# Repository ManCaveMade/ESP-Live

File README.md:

# ESP-Live
An ESP8266 (ESP-12F) board with USB and Mains power supply for home automation applications.

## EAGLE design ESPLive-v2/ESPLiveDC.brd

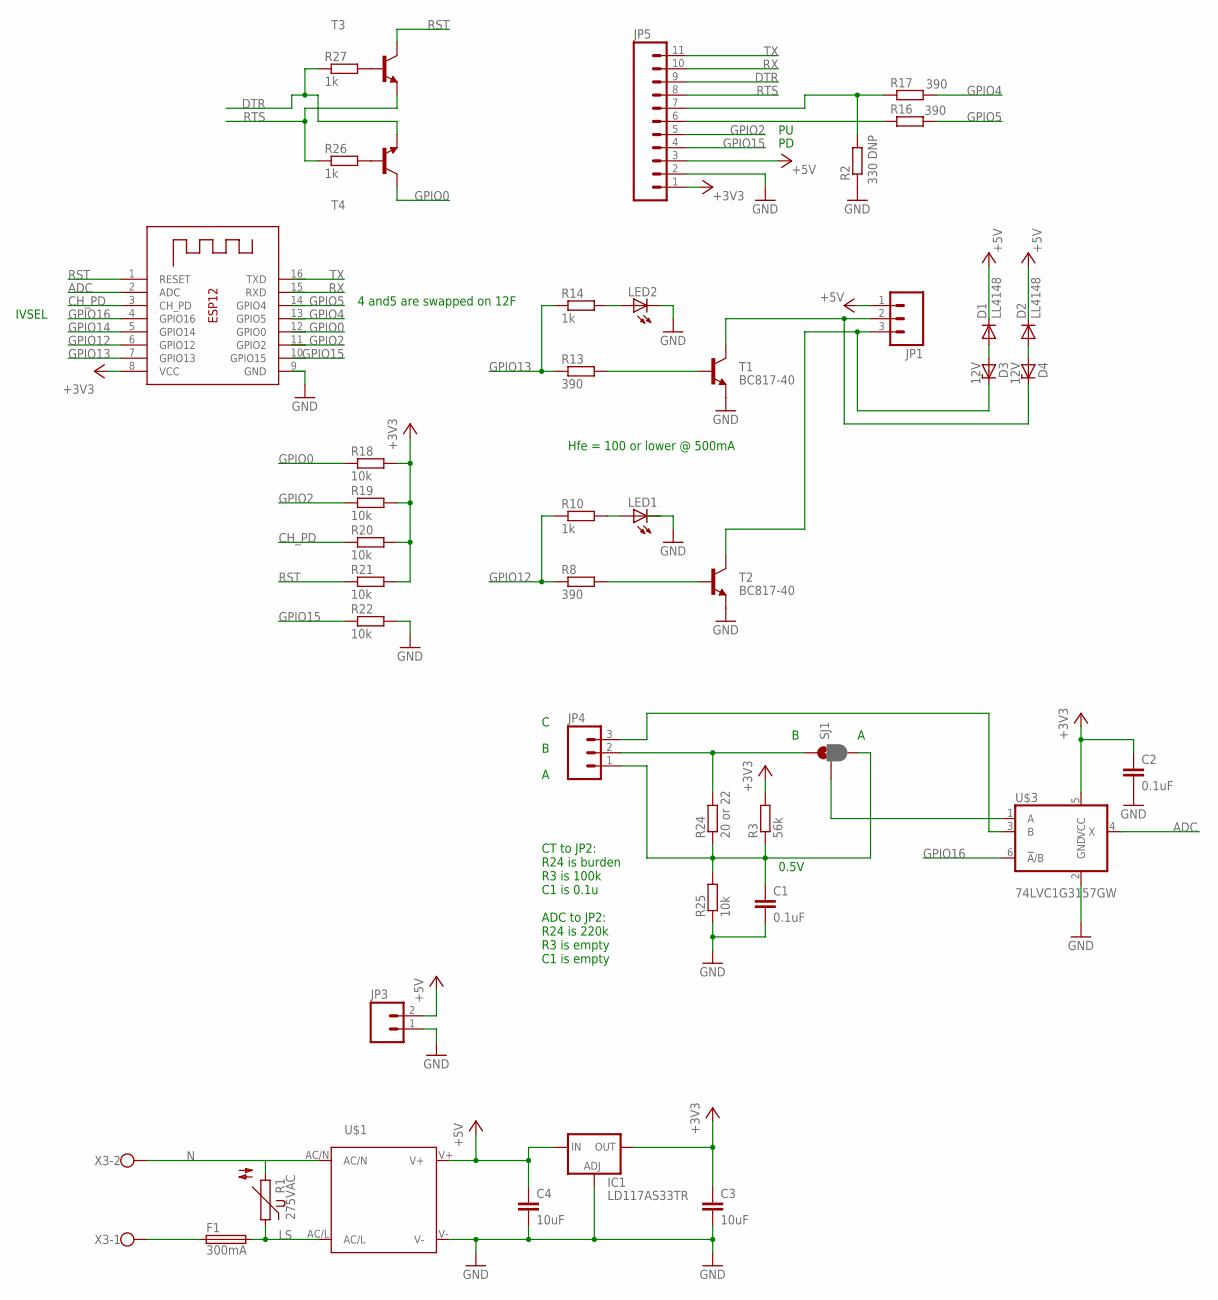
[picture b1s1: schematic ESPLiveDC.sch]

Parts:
C1, C2: 0.1uF; C0603
C3, C4: 10uF; C0805
D1, D2: LL4148; SOD80C
D3, D4: 12V; SOD80C
F1: 300mA; TE5
IC1: LD117AS33TR; SOT223
JP1, JP4: M03POLAR_LOCK; MOLEX-1X3_LOCK
JP3: M02POLAR_LOCK; MOLEX-1X2_LOCK
JP5: M11LOCK; 1X11_LOCK
LED1, LED2: LED1206; LED-1206
R1: 275VAC; P593
R2: 330 DNP; R0603
R3: 56k; R0603
R8, R13, R16, R17: 390; R0603
R10, R14, R26, R27: 1k; R0603
R18, R19, R20, R21, R22, R25: 10k; R0603
R24: 20 or 22; R1206
SJ1: JUMPER-PAD-3-2OF3_NC_BY_PASTE; PAD-JUMPER-3-2OF3_NC_BY_PASTE_YES_SILK_FULL_BOX
T1, T2: BC817-40; SOT23-BEC
T3, T4: BC817-40-NPN-SOT23-BEC; SOT23-BEC
U$1: IRM_01/02_SMDIRM_01/02_SMD; IRM_01/02_SMD
U$3: 74LVC1G3157GW; SOT363
X1: ESP-12
X3: W237-102

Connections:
+3V3: C2.1, C3.1, IC1.4 (OUT), JP5.1, R3.2, R18.2, R19.2, R20.2, R21.2, U$3.5 (VCC), X1.8 (VCC)
+5V: C4.1, D1.C, D2.C, IC1.3 (IN), JP1.1, JP3.2, JP5.3, U$1.V+
ADC: U$3.4 (X), X1.2 (ADC)
CH_PD: R20.1, X1.3 (CH_PD)
DTR: JP5.9, R27.1, T4.E
GND: C1.2, C2.2, C3.2, C4.2, IC1.1 (ADJ), JP3.1, JP5.2, LED1.C, LED2.C, R2.1, R22.2, R25.1, T1.E, T2.E, U$1.V-, U$3.2 (GND), X1.9 (GND)
GPIO0: R18.1, T4.C, X1.12 (GPIO0)
GPIO2: JP5.5, R19.1, X1.11 (GPIO2)
GPIO4: R17.2, X1.13 (GPIO5)
GPIO5: R16.2, X1.14 (GPIO4)
GPIO12: R8.1, R10.1, X1.6 (GPIO12)
GPIO13: R13.1, R14.1, X1.7 (GPIO13)
GPIO14: X1.5 (GPIO14)
GPIO15: JP5.4, R22.1, X1.10 (GPIO15)
GPIO16: U$3.6 (!A!/B), X1.4 (GPIO16)
LS: F1.2, R1.1, U$1.AC/L
N: R1.2, U$1.AC/N, X3.2
unnamed: R13.2, T1.B
unnamed: LED1.A, R10.2
unnamed: R8.2, T2.B
unnamed: D4.C, JP1.2, T1.C
unnamed: D3.C, JP1.3, T2.C
unnamed: F1.1, X3.1
unnamed: D1.A, D3.A
unnamed: D2.A, D4.A
unnamed: C1.1, JP4.1, R3.1, R24.1, R25.2, SJ1.3
unnamed: JP4.2, R24.2, SJ1.1
unnamed: SJ1.2, U$3.1 (A)
unnamed: JP4.3, U$3.3 (B)
unnamed: LED2.A, R14.2
unnamed: JP5.6, R16.1
unnamed: JP5.7, R2.2, R17.1
unnamed: R26.2, T4.B
unnamed: R27.2, T3.B
RST: R21.1, T3.C, X1.1 (RESET)
RTS: JP5.8, R26.1, T3.E
RX: JP5.10, X1.15 (RXD)
TX: JP5.11, X1.16 (TXD)

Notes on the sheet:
IVSEL
Hfe = 100 or lower @ 500mA
4 and5 are swapped on 12F
CT to JP2: R24 is burden R3 is 100k C1 is 0.1u ADC to JP2: R24 is 220k R3 is empty C1 is empty
0.5V

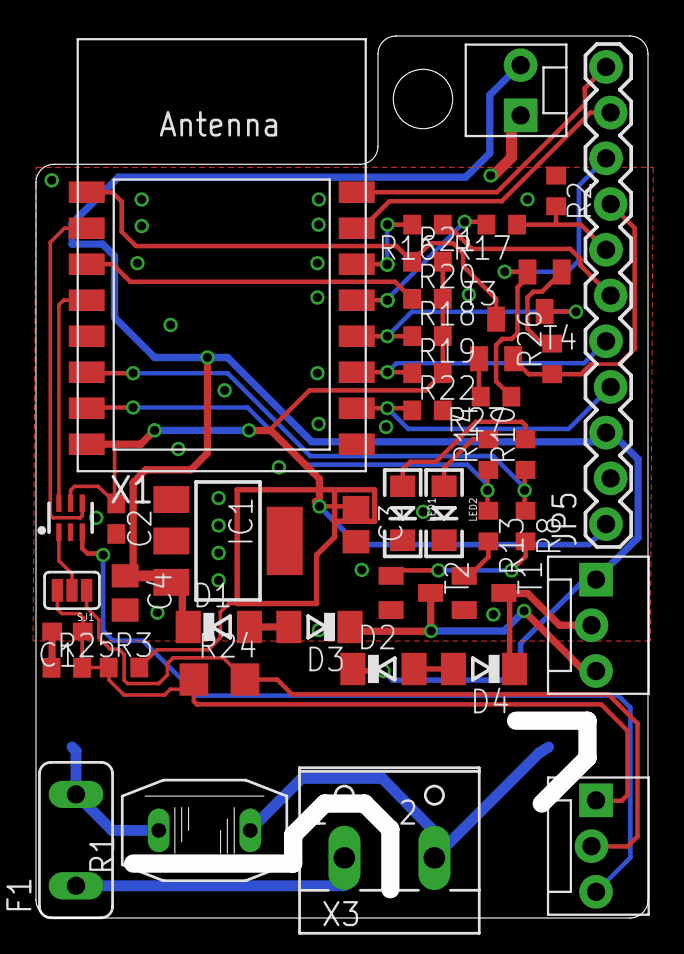
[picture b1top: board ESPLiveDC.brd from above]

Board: 2 copper layers, 34.0 x 49.0 mm, 43 parts (1 on the bottom side), 37 nets.

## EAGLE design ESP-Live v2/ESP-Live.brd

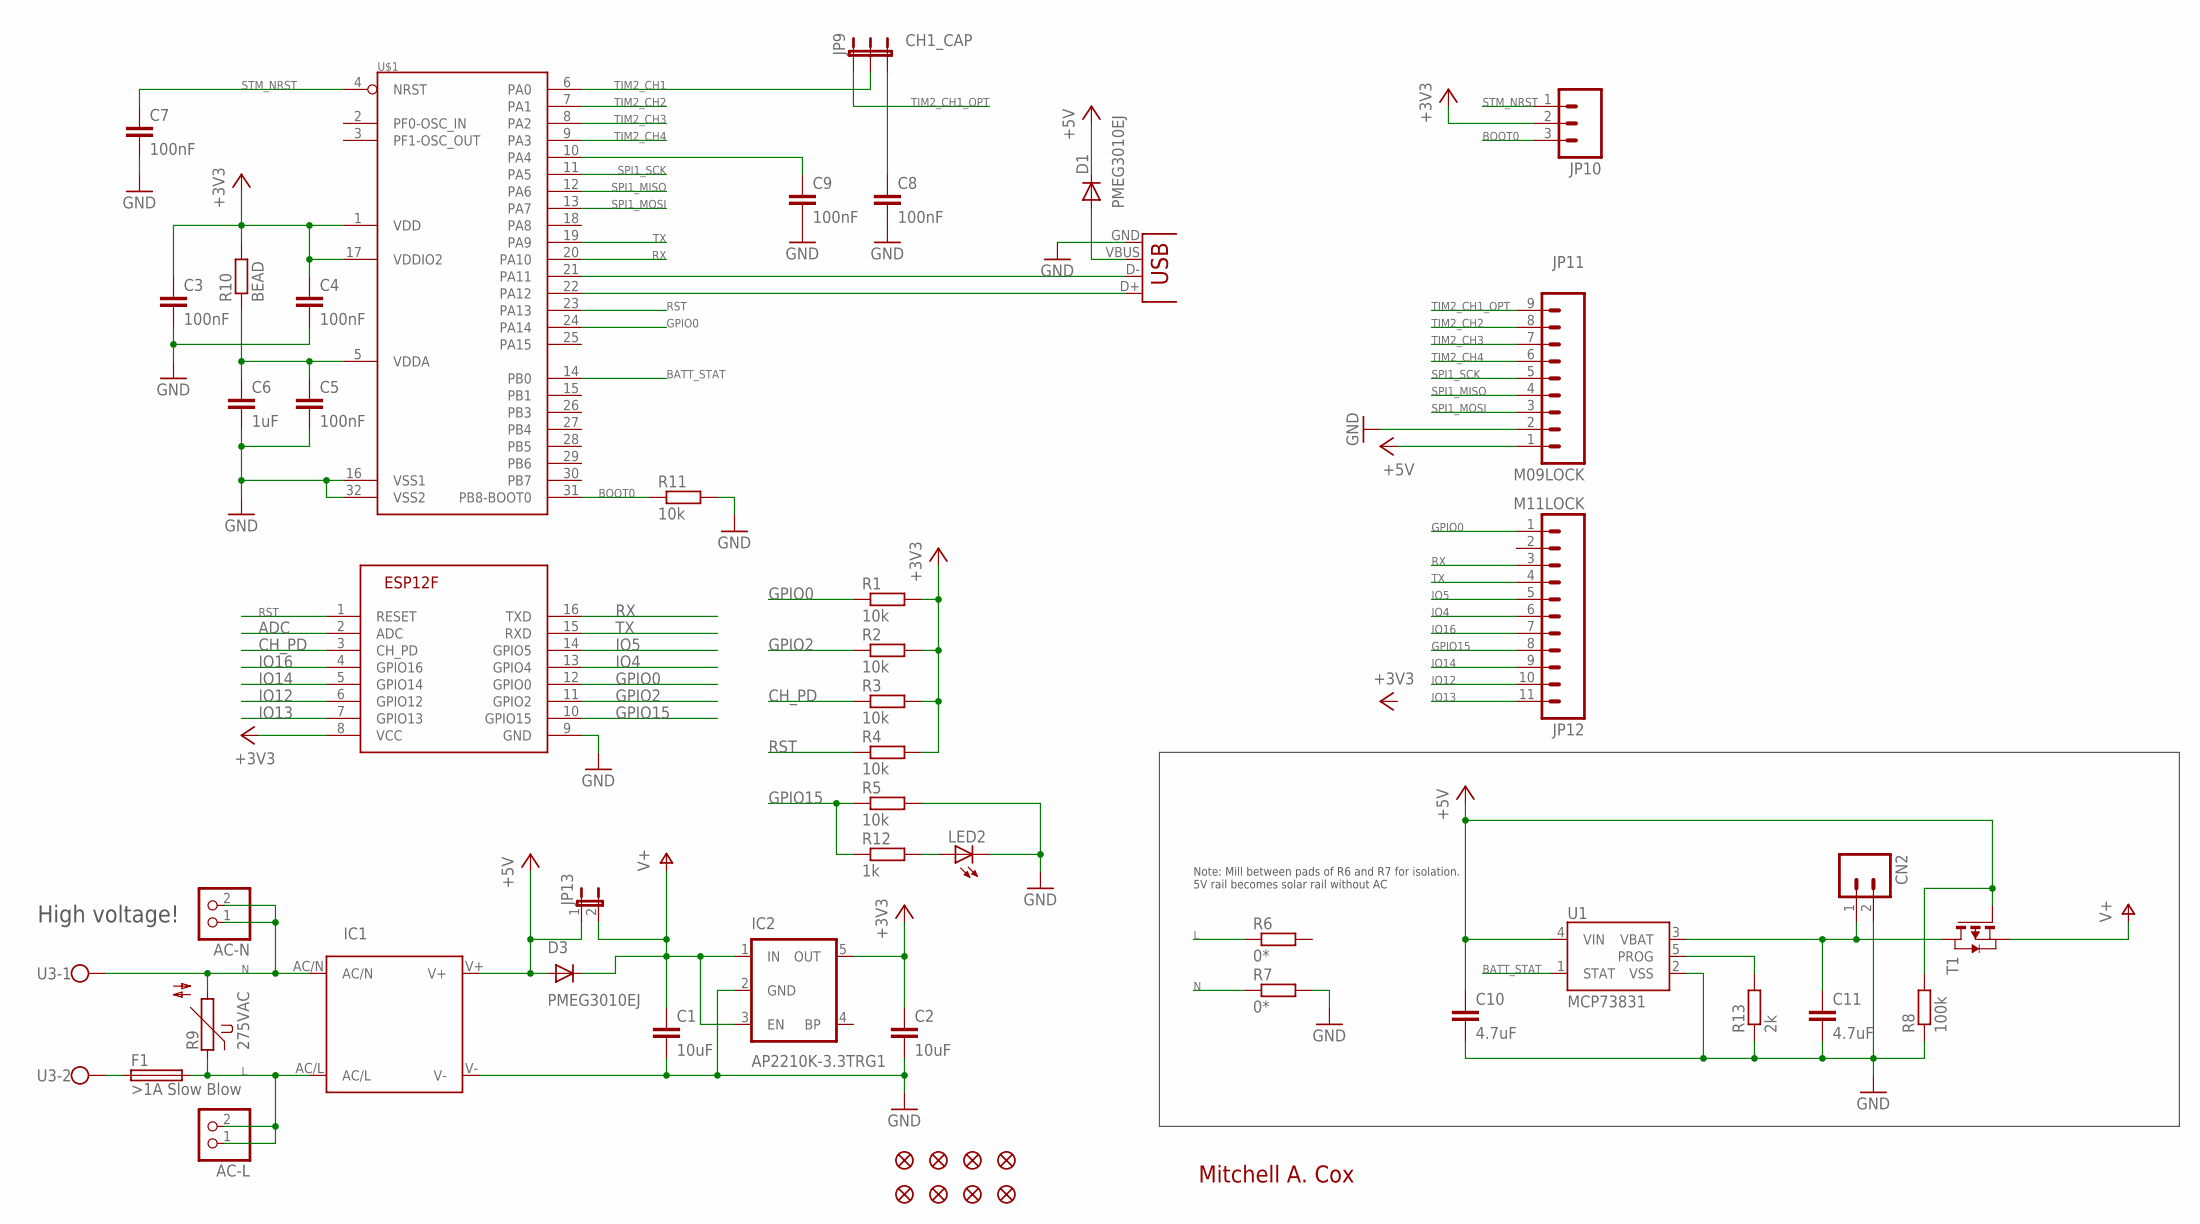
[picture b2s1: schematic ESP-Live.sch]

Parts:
AC-L: PINHD-1X2; 1X02
AC-N: PINHD-1X2; 1X02
C1, C2: 10uF; C0805
C3, C4, C5, C7, C8, C9: 100nF; C0603
C6: 1uF; C0805
C10, C11: 4.7uF; C0805
CN1: USBSMD; USB-MINIB
CN2: M02-JST-2-PTH-NO_SILK; JST-2-PTH-NS
D1, D3: PMEG3010EJ; SOD-323
F1: >1A Slow Blow; TE5
IC1: IRM_01/02_SMDIRM_01/02_SMD; IRM_01/02_SMD
IC2: AP2210K-3.3TRG1; SOT23-5
IC3: ESP-12F
JP1, JP2, JP3, JP4, JP5, JP6, JP7, JP8: FIDUCIAL1X2; FIDUCIAL-1X2
JP9: CH1_CAP; SJ_3_PASTE1&2
JP10: M03LOCK; 1X03_LOCK
JP11: M09LOCK; 1X09_LOCK
JP12: M11LOCK; 1X11_LOCK
JP13: JUMPER-2SMD-NO; SJ_2S-NO
LED2: LEDCHIPLED_0805; CHIPLED_0805
R1, R2, R3, R4, R5, R11: 10k; R0603
R6, R7: 0*; R2512
R8: 100k; R0603
R9: 275VAC; P593
R10: BEAD; R0603
R12: 1k; R0603
R13: 2k; R0603
T1: PMOSSOT23; SOT-23
U1: MCP73831; SOT23-5
U3: W237-102
U$1: STM32F042K; LQFP32

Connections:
+3V3: C2.1, C3.1, C4.1, IC2.5 (OUT), IC3.8 (VCC), JP10.2, R1.2, R2.2, R3.2, R4.2, R10.2, U$1.1 (VDD), U$1.17 (VDDIO2)
+5V: C10.1, D1.1 (C), D3.2 (A), IC1.V+, JP11.1, JP13.1, R8.2, T1.3 (G), U1.4 (VIN)
ADC: IC3.2 (ADC)
BATT_STAT: U1.1 (STAT), U$1.14 (PB0)
BOOT0: JP10.3, R11.1, U$1.31 (PB8-BOOT0)
CH_PD: IC3.3 (CH_PD), R3.1
GND: C1.2, C2.2, C3.2, C4.2, C5.2, C6.2, C7.2, C8.2, C9.2, C10.2, C11.2, CN1.GND, CN2.2, IC1.V-, IC2.2 (GND), IC3.9 (GND), JP11.2, LED2.C, R5.2, R7.2, R8.1, R11.2, R13.1, U1.2 (VSS), U$1.16 (VSS1), U$1.32 (VSS2)
GPIO0: IC3.12 (GPIO0), JP12.1, R1.1, U$1.24 (PA14)
GPIO2: IC3.11 (GPIO2), R2.1
GPIO15: IC3.10 (GPIO15), JP12.8, R5.1, R12.1
IO4: IC3.13 (GPIO4), JP12.6
IO5: IC3.14 (GPIO5), JP12.5
IO12: IC3.6 (GPIO12), JP12.10
IO13: IC3.7 (GPIO13), JP12.11
IO14: IC3.5 (GPIO14), JP12.9
IO16: IC3.4 (GPIO16), JP12.7
L: AC-L.1, AC-L.2, F1.2, IC1.AC/L, R6.1, R9.1
N: AC-N.1, AC-N.2, IC1.AC/N, R7.1, R9.2, U3.1
unnamed: F1.1, U3.2
unnamed: C5.1, C6.1, R10.1, U$1.5 (VDDA)
unnamed: R13.2, U1.5 (PROG)
unnamed: CN1.D-, U$1.21 (PA11)
unnamed: CN1.D+, U$1.22 (PA12)
unnamed: CN1.VBUS, D1.2 (A)
unnamed: LED2.A, R12.2
unnamed: C9.1, U$1.10 (PA4)
unnamed: C8.1, JP9.3
unnamed: C11.1, CN2.1, T1.1 (D), U1.3 (VBAT)
RST: IC3.1 (RESET), R4.1, U$1.23 (PA13)
RX: IC3.16 (TXD), JP12.3, U$1.20 (PA10)
SPI1_MISO: JP11.4, U$1.12 (PA6)
SPI1_MOSI: JP11.3, U$1.13 (PA7)
SPI1_SCK: JP11.5, U$1.11 (PA5)
STM_NRST: C7.1, JP10.1, U$1.4 (NRST)
TIM2_CH1: JP9.2, U$1.6 (PA0)
TIM2_CH1_OPT: JP9.1, JP11.9
TIM2_CH2: JP11.8, U$1.7 (PA1)
TIM2_CH3: JP11.7, U$1.8 (PA2)
TIM2_CH4: JP11.6, U$1.9 (PA3)
TX: IC3.15 (RXD), JP12.4, U$1.19 (PA9)
V+: C1.1, D3.1 (C), IC2.1 (IN), IC2.3 (EN), JP13.2, T1.2 (S)

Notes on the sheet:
Mitchell A. Cox
High voltage!
Note: Mill between pads of R6 and R7 for isolation. 5V rail becomes solar rail without AC

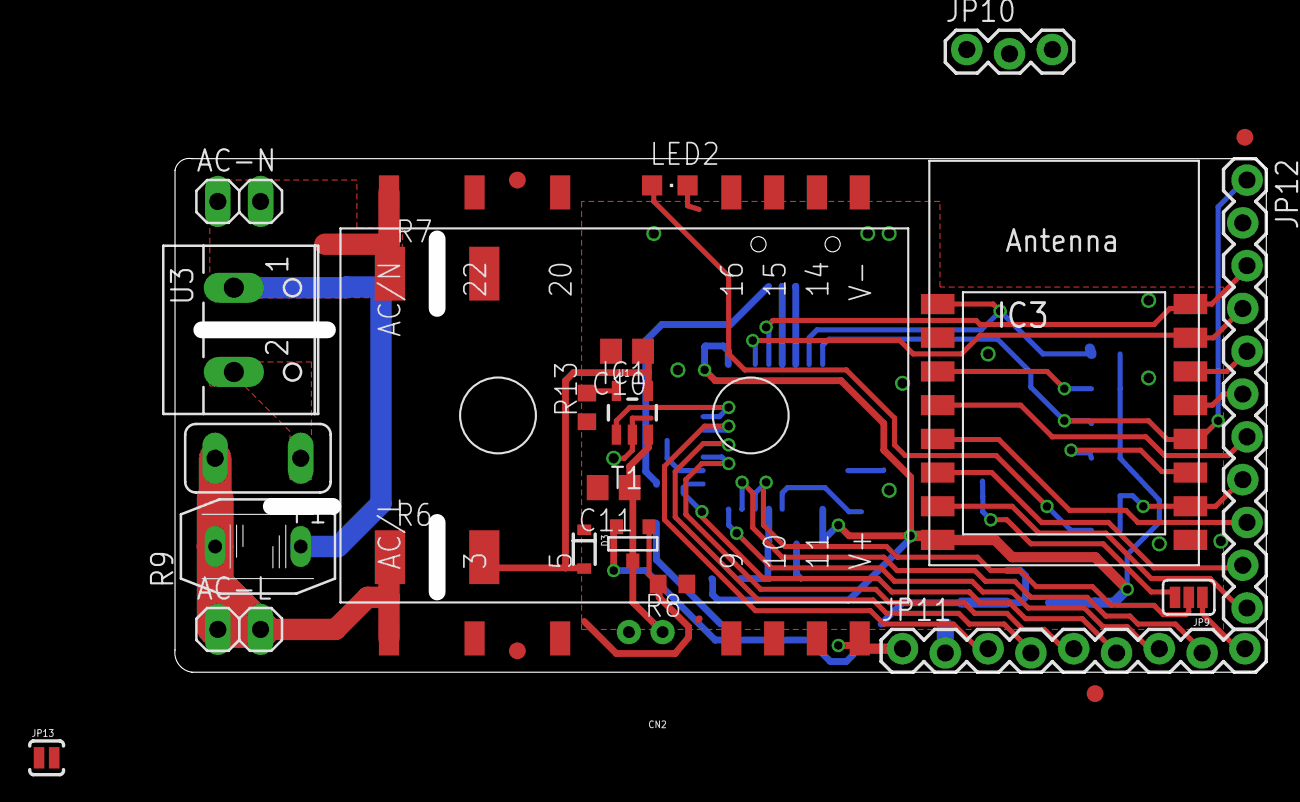
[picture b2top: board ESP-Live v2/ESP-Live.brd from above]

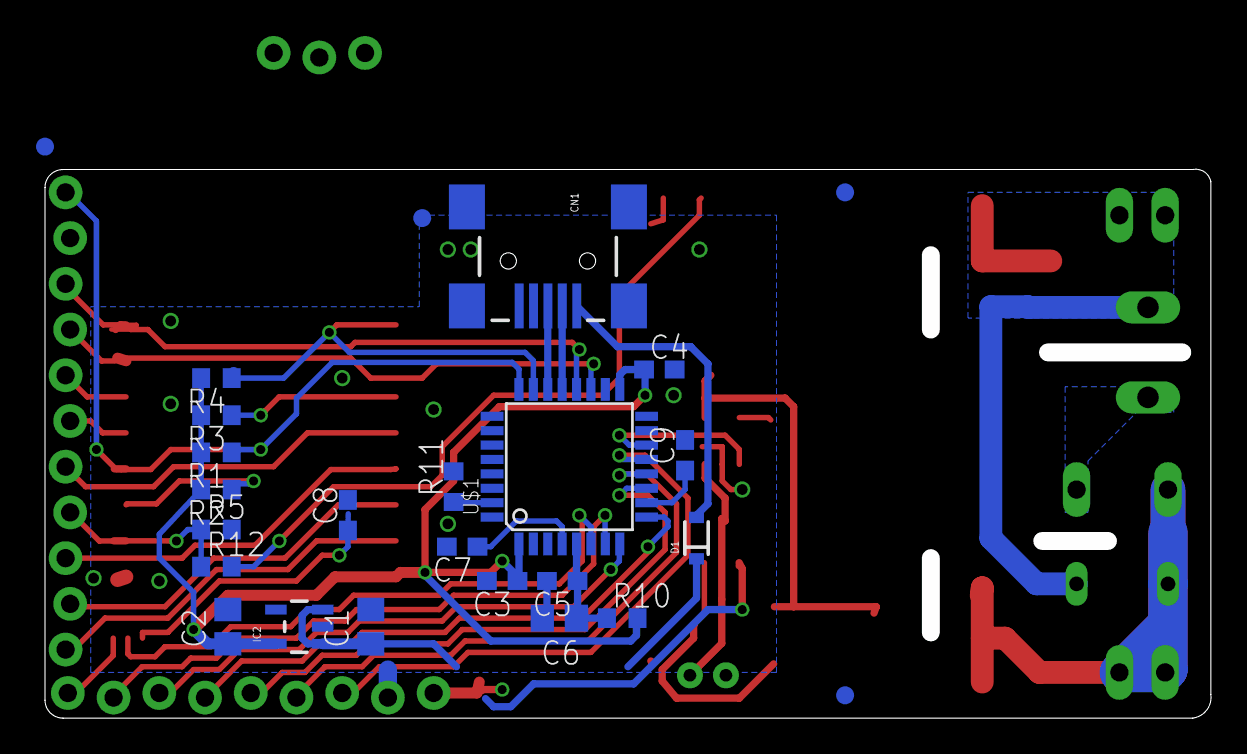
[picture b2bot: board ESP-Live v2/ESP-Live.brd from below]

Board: 2 copper layers, 64.8 x 30.5 mm, 52 parts (25 on the bottom side), 40 nets.

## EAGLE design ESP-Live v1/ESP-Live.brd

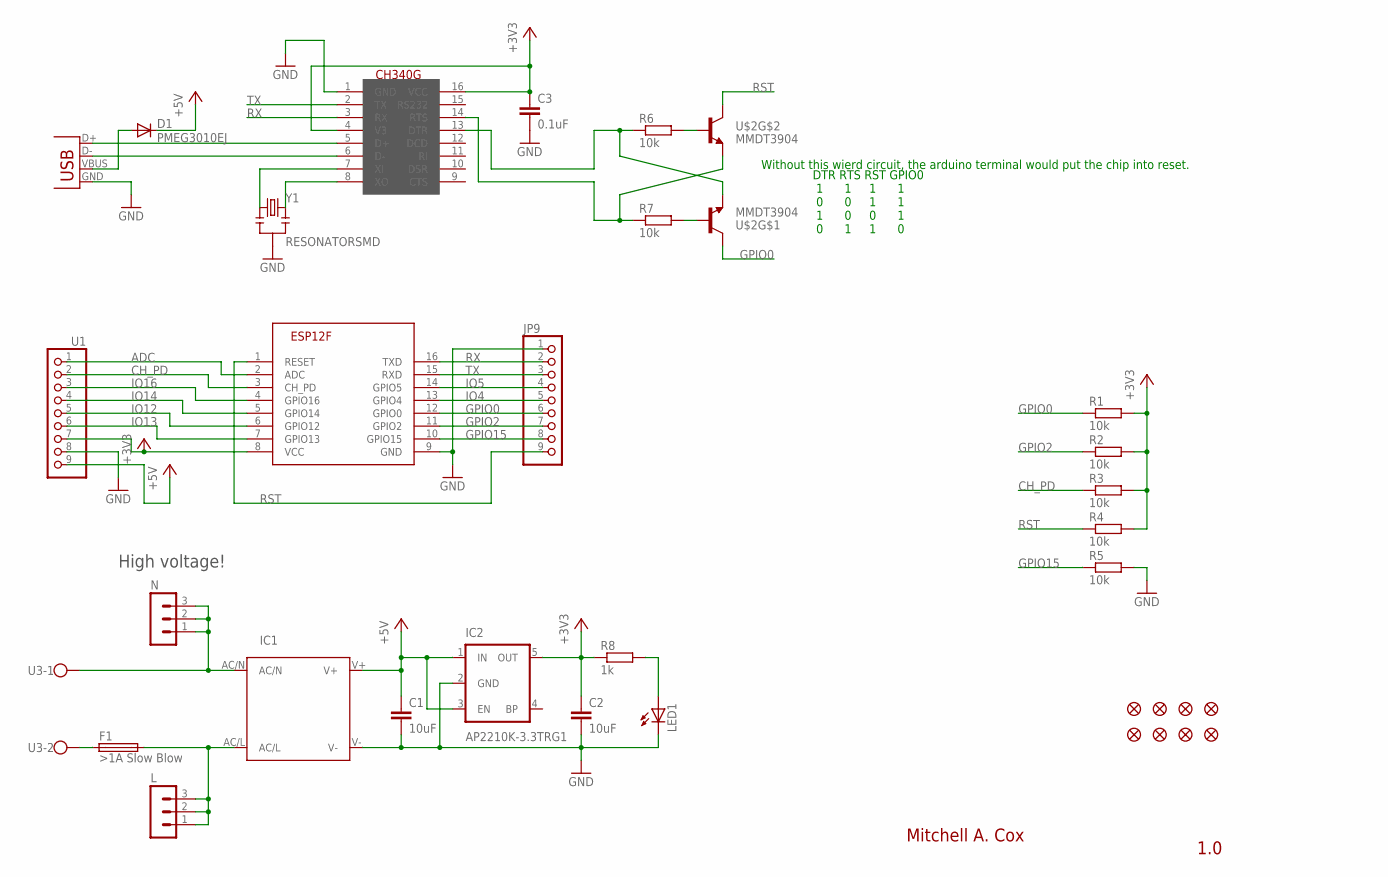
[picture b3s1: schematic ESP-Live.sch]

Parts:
C1, C2: 10uF; C0805
C3: 0.1uF; C0805
CN1: USBSMD; USB-MINIB
D1: PMEG3010EJ; SOD-323
F1: >1A Slow Blow; TE5
IC1: IRM_01/02_SMDIRM_01/02_SMD; IRM_01/02_SMD
IC2: AP2210K-3.3TRG1; SOT23-5
IC3: ESP-12F
JP1, JP2, JP3, JP4, JP5, JP6, JP7, JP8: FIDUCIAL1X2; FIDUCIAL-1X2
JP9: PINHD-1X9; 1X09-BIG
L: MA03-1
LED1: LEDCHIPLED_0805; CHIPLED_0805
N: MA03-1
R1, R2, R3, R4, R5, R6, R7: 10k; M0805
R8: 1k; M0805
U1: PINHD-1X9; 1X09-BIG
U3: W237-113
U$1: CH340G; SOIC16
U$2: MMDT3904; SOT363
Y1: RESONATORSMD; RESONATOR-SMD

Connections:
+3V3: C2.1, C3.1, IC2.5 (OUT), IC3.8 (VCC), R1.2, R2.2, R3.2, R4.2, R8.1, U1.7, U$1.4 (V3), U$1.16 (VCC)
+5V: C1.1, D1.1 (C), IC1.V+, IC2.1 (IN), IC2.3 (EN), U1.9
ADC: IC3.2 (ADC), U1.1
CH_PD: IC3.3 (CH_PD), R3.1, U1.2
GND: C1.2, C2.2, C3.2, CN1.GND, IC1.V-, IC2.2 (GND), IC3.9 (GND), JP9.1, LED1.C, R5.2, U1.8, U$1.1 (GND), Y1.2
GPIO0: IC3.12 (GPIO0), JP9.6, R1.1, U$2.3 (C)
GPIO2: IC3.11 (GPIO2), JP9.7, R2.1
GPIO15: IC3.10 (GPIO15), JP9.8, R5.1
IO4: IC3.13 (GPIO4), JP9.5
IO5: IC3.14 (GPIO5), JP9.4
IO12: IC3.6 (GPIO12), U1.5
IO13: IC3.7 (GPIO13), U1.6
IO14: IC3.5 (GPIO14), U1.4
IO16: IC3.4 (GPIO16), U1.3
unnamed: F1.1, U3.2
unnamed: IC1.AC/N, N.1, N.2, N.3, U3.1
unnamed: F1.2, IC1.AC/L, L.1, L.2, L.3
unnamed: LED1.A, R8.2
unnamed: R7.2, U$2.5 (B)
unnamed: R6.2, U$2.2 (B)
unnamed: R6.1, U$1.13 (DTR), U$2.4 (E)
unnamed: CN1.D+, U$1.5 (D+)
unnamed: R7.1, U$1.14 (RTS), U$2.1 (E)
unnamed: CN1.D-, U$1.6 (D-)
unnamed: CN1.VBUS, D1.2 (A)
unnamed: U$1.7 (XI), Y1.1
unnamed: U$1.8 (XO), Y1.3
RST: IC3.1 (RESET), JP9.9, R4.1, U$2.6 (C)
RX: IC3.16 (TXD), JP9.2, U$1.3 (RX)
TX: IC3.15 (RXD), JP9.3, U$1.2 (TX)

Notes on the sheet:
Without this wierd circuit, the arduino terminal would put the chip into reset.
DTR RTS RST GPIO0 1 1 1 1 0 0 1 1 1 0 0 1 0 1 1 0
Mitchell A. Cox
1.0
High voltage!

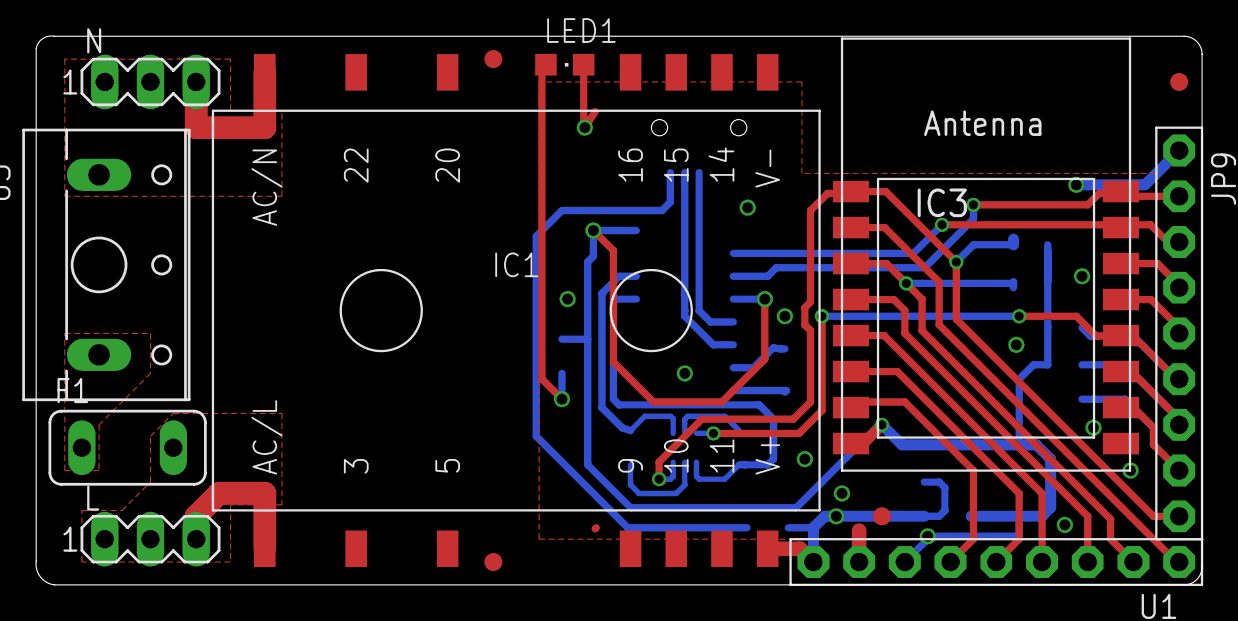
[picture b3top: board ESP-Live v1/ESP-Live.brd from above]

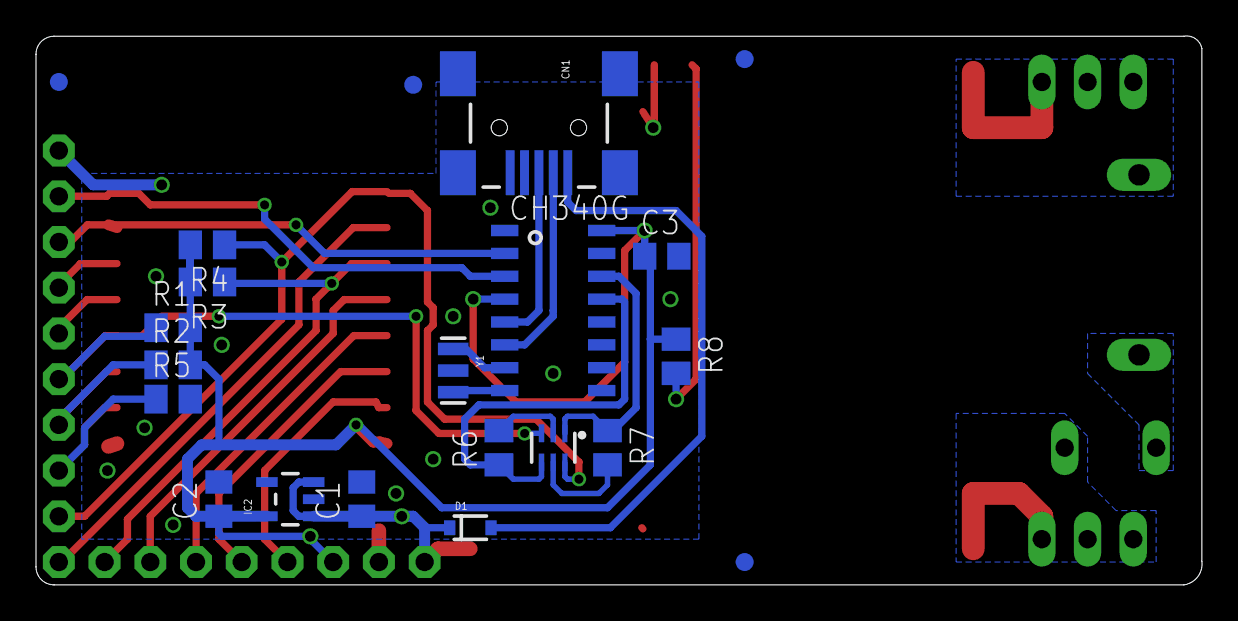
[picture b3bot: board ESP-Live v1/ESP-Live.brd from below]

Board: 2 copper layers, 64.8 x 30.5 mm, 34 parts (21 on the bottom side), 30 nets.

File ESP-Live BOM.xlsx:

Part | Description | Quantity | MOQ | Price Each | Cost | Total | Supplier Link | Datasheet Link
 | ESP-12F | 1
 | CH340G | 1
Y1 | 12 MHz Resonator | 1
 | PMEG3101EJ | 1 |  |  |  |  | http://za.rs-online.com/web/p/rectifier-schottky-diodes/0485537/
 | USB Mini connector | 1
 | 8 pin header | 1
 | 10 pin header | 1
 | Fuse, 1A, TE5 | 1 |  |  |  |  | http://www.mouser.co.uk/ProductDetail/Bel-Fuse/RST-2/?qs=sGA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
 | IRM-02-05S PSU Module | 1 |  | 80 |  |  | http://www.mouser.co.uk/ProductDetail/Mean-Well/IRM-02-5S/?q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
 | AP2210K-3.3TRG1 | 1 |  | 5.39 |  |  | http://www.mouser.co.uk/ProductDetail/Diodes-Incorporated/AP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
 | MMDT3904 dual NPN | 1 |  | 5 |  |  | http://www.mouser.co.uk/ProductDetail/Diodes-Incorporated/MM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
 | 3 pin header | 2 |  |  |  |  | http://uk.rs-online.com/web/p/pcb-sockets/6816810/
 | 10k 0805 | 7
 | 1k 0805 | 1
 | LED 0805 | 1
 | 10uF 0805 | 2
 | 0.1uF 0805 | 1

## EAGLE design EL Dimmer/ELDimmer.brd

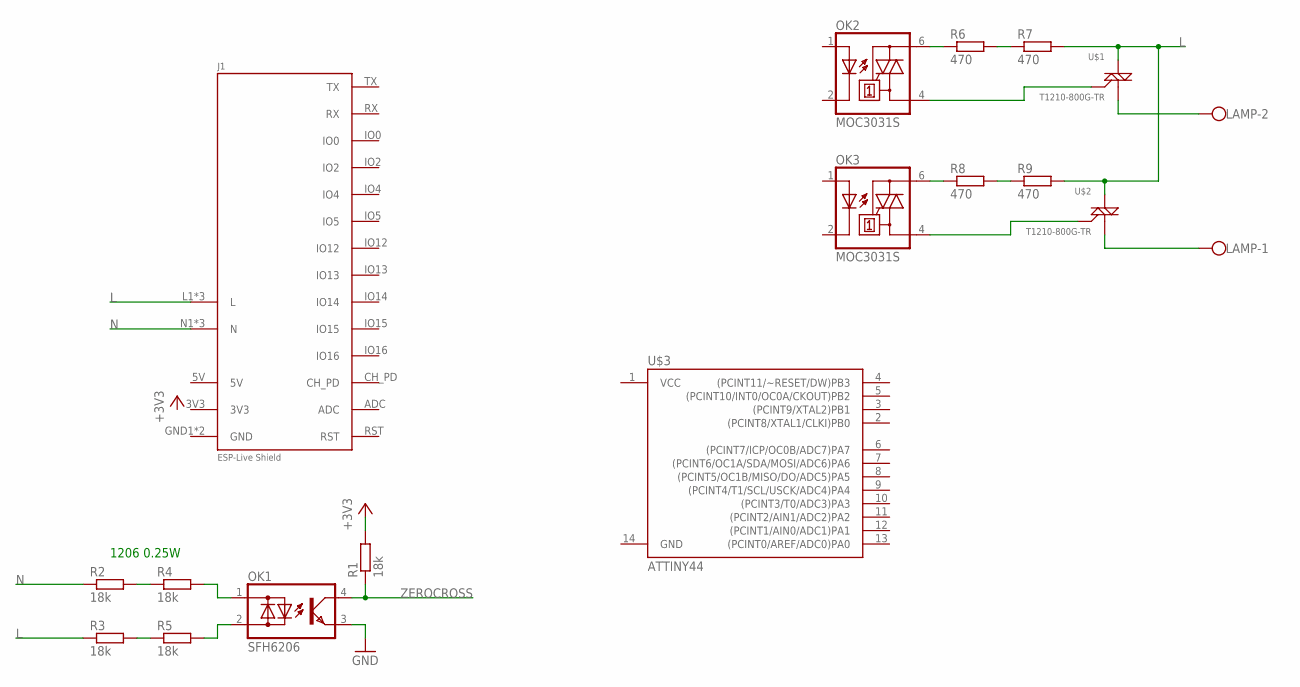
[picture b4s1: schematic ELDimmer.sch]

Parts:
J1: ESP-LIVE-SHIELD
LAMP: W237-102
OK1: SFH6206; DIL4-SMD
OK2, OK3: MOC3031S; DIL6-SMD
R1, R2, R3, R4, R5: 18k; R1206
R6, R7, R8, R9: 470; R1206
U$1, U$2: T1210-800G-TR; D2PAK
U$3: ATTINY44; SO14

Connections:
3V3: J1.3V3
5V: J1.5V
+3V3: R1.2
GND: J1.GND1 (GND), J1.GND2 (GND), OK1.3 (E)
L: J1.L1 (L), J1.L2 (L), J1.L3 (L), R3.1, R7.2, R9.2, U$1.2 (A2), U$1.TAB (A2), U$2.2 (A2), U$2.TAB (A2)
N: J1.N1 (N), J1.N2 (N), J1.N3 (N), R2.1
unnamed: R2.2, R4.1
unnamed: R3.2, R5.1
unnamed: OK1.1 (AC1), R4.2
unnamed: OK1.2 (AC2), R5.2
unnamed: R6.2, R7.1
unnamed: R8.2, R9.1
unnamed: OK2.6 (A2), R6.1
unnamed: OK2.4 (A1), U$1.3 (G)
unnamed: LAMP.2, U$1.1 (A1)
unnamed: LAMP.1, U$2.1 (A1)
unnamed: OK3.4 (A1), U$2.3 (G)
unnamed: OK3.6 (A2), R8.1
ZEROCROSS: OK1.4 (C), R1.1

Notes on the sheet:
1206 0.25W

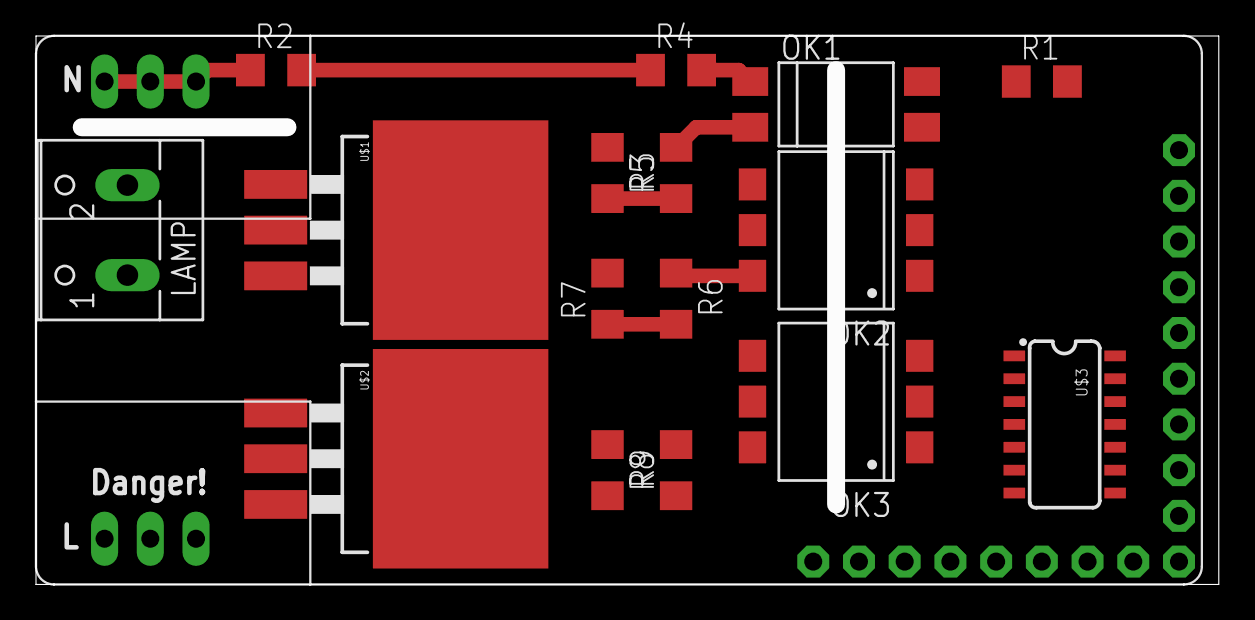
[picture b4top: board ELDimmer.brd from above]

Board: 2 copper layers, 65.7 x 30.5 mm, 17 parts (0 on the bottom side), 16 nets.

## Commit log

2016-12-27 Version 1. Works perfectly but have not tested the CH340 yet.
2016-12-27 Added v2 directory, ready for some significant enhancements to the design:
    * Remove CH340 and replace with STM32 with USB-CDC
    * Use the STM32 for analog functions + PWM, etc. since ESP is bad at that
    * Implement connections from ESP for OTA programming of STM32 (if possible)
    * Make pins on ESP-Live dual role / remove the useless ones from the ESP such as ADC, CH_PD, etc. and connect directly to STM32 intead.
2017-01-08 with batery charger
2017-08-18 added esplive v2

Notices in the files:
parts and their libraries:
SparkFun-DigitalIC: Licensing: Creative Commons ShareAlike 4.0 International - https://creativecommons.org/licenses/by-sa/4.0
SparkFun: Licensing: CC v3.0 Share-Alike You are welcome to use this library for commercial purposes.
